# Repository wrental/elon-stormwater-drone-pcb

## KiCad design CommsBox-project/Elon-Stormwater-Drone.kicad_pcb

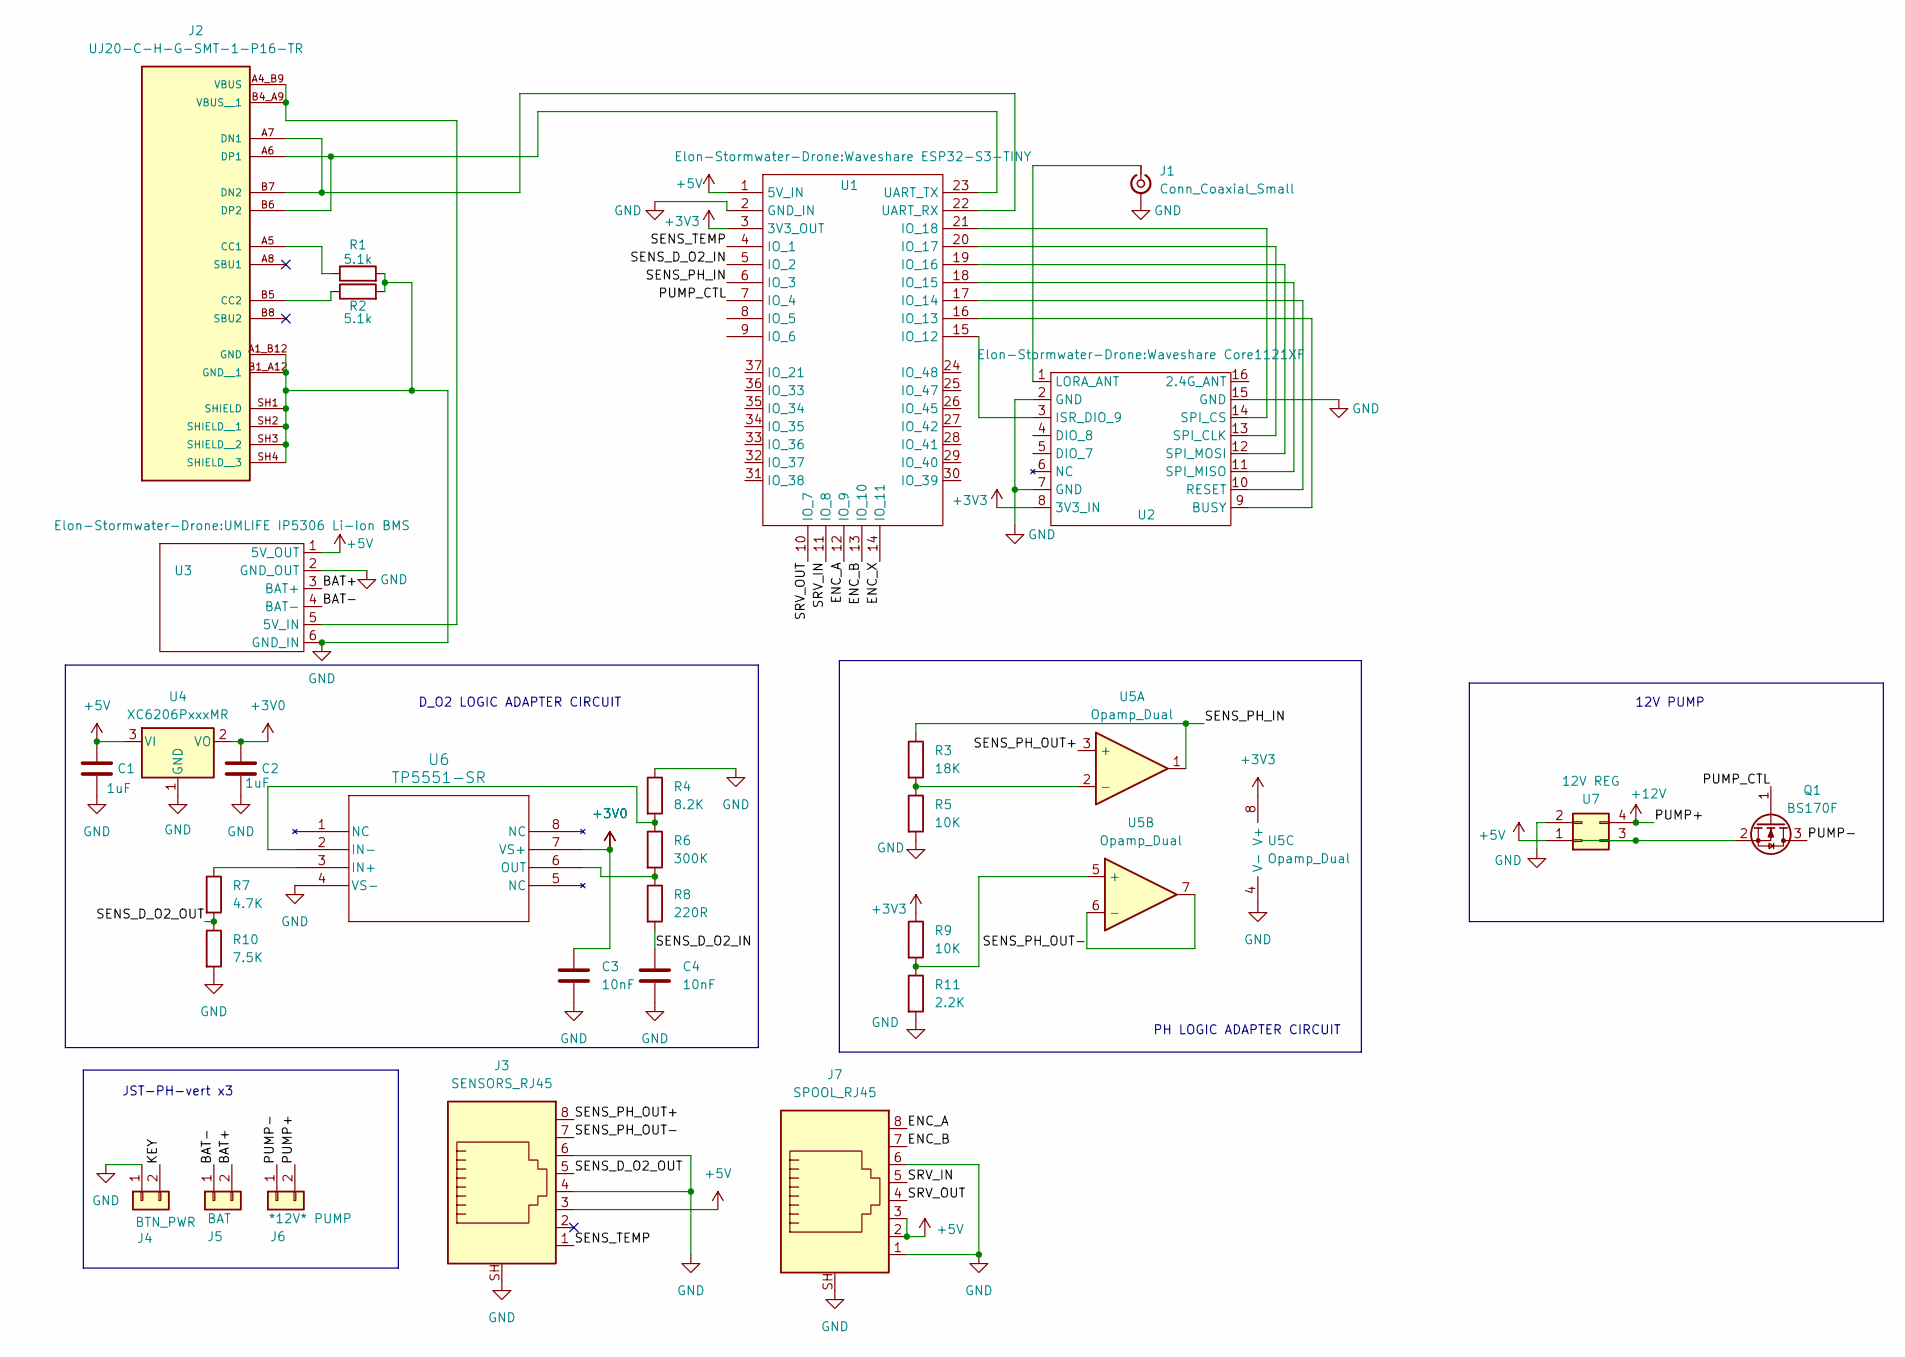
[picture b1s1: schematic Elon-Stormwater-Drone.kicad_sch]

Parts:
C1, C2: 1uF; C_0603_1608Metric
C3, C4: 10nF; C_0603_1608Metric
J1: Conn_Coaxial_Small; SMA_Amphenol_132289_EdgeMount
J2: UJ20-C-H-G-SMT-1-P16-TR; SAMESKY_UJ20-C-H-G-SMT-1-P16-TR; PARTREV 1.0
J3: SENSORS_RJ45; RJ45_Molex_0855135013_Vertical
J4: BTN_PWR; JST_PH_B2B-PH-K_1x02_P2.00mm_Vertical
J5: BAT; JST_PH_B2B-PH-K_1x02_P2.00mm_Vertical
J6: *12V* PUMP; JST_PH_B2B-PH-K_1x02_P2.00mm_Vertical
J7: SPOOL_RJ45; RJ45_Molex_0855135013_Vertical
Q1: BS170F; SOT-23
R1, R2: 5.1k; R_0603_1608Metric
R3: 18K; R_0603_1608Metric
R4: 8.2K; R_0603_1608Metric
R5, R9: 10K; R_0603_1608Metric
R6: 300K; R_0603_1608Metric
R7: 4.7K; R_0603_1608Metric
R8: 220R; R_0603_1608Metric
R10: 7.5K; R_0603_1608Metric
R11: 2.2K; R_0603_1608Metric
U1: Waveshare ESP32-S3-TINY
U2: Waveshare Core1121XF
U3: UMLIFE IP5306 Li-Ion BMS
U4: XC6206PxxxMR; SOT-23-3
U5: Opamp_Dual; SOIC-8_5.3x6.2mm_P1.27mm
U6: TP5551-SR; SO1SOP-8-A_TPK
U7: 12V REG; DC-DC BOOST

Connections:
+3V0: C2.1, C3.1, U4.2 (VO), U6.7 (VS+)
+3V3: R9.1, U1.3 (3V3_OUT), U2.8 (3V3_IN), U5.8 (V+)
+5V: C1.1, J3.3, J7.2, J7.3, U1.1 (5V_IN), U3.1 (5V_OUT), U4.3 (VI), U7.1
+12V: J6.2, U7.4
/BAT+: J5.2, U3.3 (BAT+)
/BAT-: J5.1, U3.4 (BAT-)
/ENC_A: J7.8, U1.12 (IO_9)
/ENC_B: J7.7, U1.13 (IO_10)
/ENC_X: U1.14 (IO_11)
/KEY: J4.2
/PUMP-: J6.1, Q1.3 (D)
/PUMP_CTL: Q1.1 (G), U1.7 (IO_4)
/SENS_D_O2_IN: C4.1, R8.2, U1.5 (IO_2)
/SENS_D_O2_OUT: J3.5, R7.2, R10.1
/SENS_PH_IN: R3.1, U1.6 (IO_3), U5.1
/SENS_PH_OUT+: J3.8, U5.3 (+)
/SENS_PH_OUT-: J3.7, U5.6 (-), U5.7
/SENS_TEMP: J3.1, U1.4 (IO_1)
/SRV_IN: J7.5, U1.11 (IO_8)
/SRV_OUT: J7.4, U1.10 (IO_7)
GND: C1.2, C2.2, C3.2, C4.2, J1.2 (Ext), J2.A1_B12 (GND), J2.B1_A12 (GND__1), J2.SH1 (SHIELD), J2.SH2 (SHIELD__1), J2.SH3 (SHIELD__2), J2.SH4 (SHIELD__3), J3.4, J3.6, J3.L, J3.SH, J4.1, J7.1, J7.6, J7.L, J7.SH, R1.2, R2.2, R4.1, R5.2, R10.2, R11.2, U1.2 (GND_IN), U2.2 (GND), U2.7 (GND), U2.15 (GND), U3.2 (GND_OUT), U3.6 (GND_IN), U4.1 (GND), U5.4 (V-), U6.4 (VS-), U7.2
unnamed: J1.1 (In), U2.1 (LORA_ANT)
unnamed: J2.A5 (CC1), R1.1
unnamed: J2.B5 (CC2), R2.1
unnamed: J2.A7 (DN1), J2.B7 (DN2), U1.22 (UART_RX)
unnamed: J2.A6 (DP1), J2.B6 (DP2), U1.23 (UART_TX)
unnamed: J2.A4_B9 (VBUS), J2.B4_A9 (VBUS__1), U3.5 (5V_IN)
unnamed: Q1.2 (S), U7.3
unnamed: U1.15 (IO_12), U2.3 (ISR_DIO_9)
unnamed: U1.16 (IO_13), U2.9 (BUSY)
unnamed: U1.17 (IO_14), U2.10 (RESET)
unnamed: U1.18 (IO_15), U2.11 (SPI_MISO)
unnamed: U1.19 (IO_16), U2.12 (SPI_MOSI)
unnamed: U1.20 (IO_17), U2.13 (SPI_CLK)
unnamed: U1.21 (IO_18), U2.14 (SPI_CS)
unnamed: R3.2, R5.1, U5.2 (-)
unnamed: R9.2, R11.1, U5.5 (+)
unnamed: R7.1, U6.3 (IN+)
unnamed: R4.2, R6.1, U6.2 (IN-)
unnamed: R6.2, R8.1, U6.6 (OUT)

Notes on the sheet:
PH LOGIC ADAPTER CIRCUIT
12V PUMP
JST-PH-vert x3
D_O2 LOGIC ADAPTER CIRCUIT

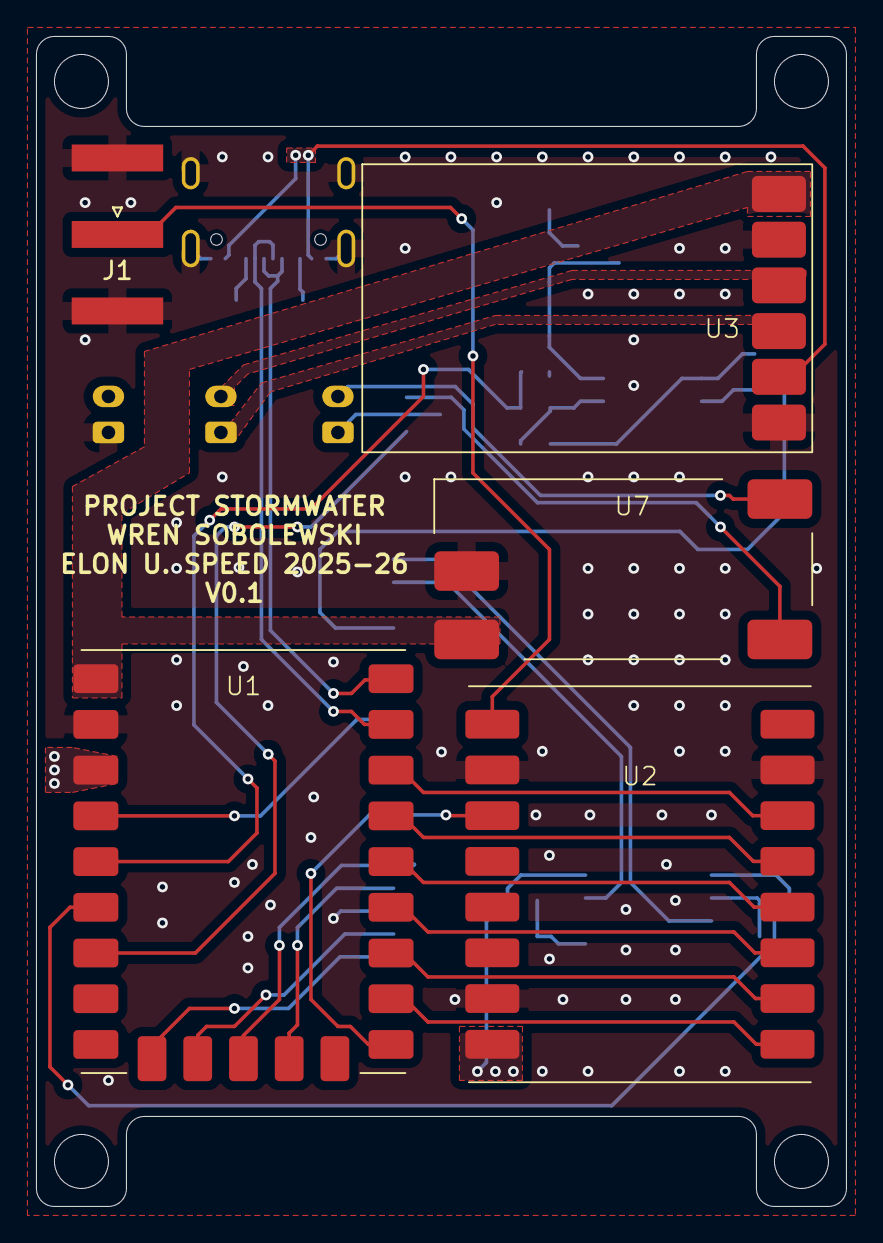
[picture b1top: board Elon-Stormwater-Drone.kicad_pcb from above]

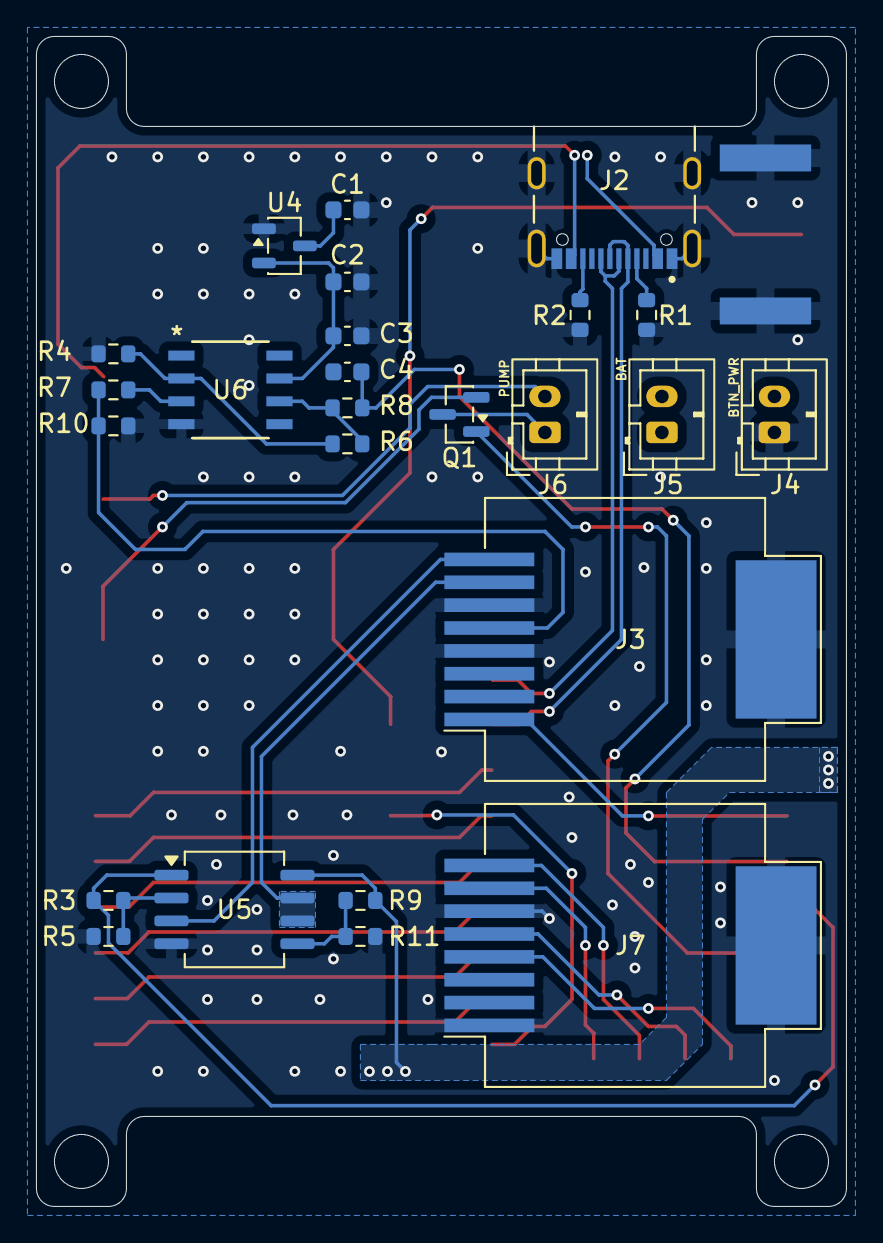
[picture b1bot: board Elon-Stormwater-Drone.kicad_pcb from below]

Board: 2 copper layers, 45.0 x 65.0 mm, 30 parts (25 on the bottom side), 38 nets.

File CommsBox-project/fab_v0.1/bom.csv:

Designator,Footprint,Quantity,Value,LCSC Part #
"C1, C2",603,2,1uF,C15849
"C3, C4",603,2,10nF,C57112
J2,SAMESKY_UJ20-C-H-G-SMT-1-P16-TR,1,UJ20-C-H-G-SMT-1-P16-TR,C45082766
"J3, J7",RJ45_Molex_0855135013_Vertical,1,,C6355995
Q1,SOT-23,1,BS170F,C20917
"R1, R2",603,2,5.1k,C23186
R10,603,1,7.5K,C23234
R11,603,1,2.2K,C4190
R3,603,1,18K,C25810
R4,603,1,8.2K,C25981
"R5, R9",603,2,10K,C25804
R6,603,1,300K,C23024
R7,603,1,4.7K,C23162
R8,603,1,220R,C22962
U4,SOT-23-3,1,XC6206PxxxMR,C22466435
U5,SOIC-8_5.3x6.2mm_P1.27mm,1,Opamp_Dual,C4370389
U6,SO1SOP-8-A_TPK,1,TP5551-SR,C47126865

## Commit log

2026-05-07 init
2026-05-14 final update
